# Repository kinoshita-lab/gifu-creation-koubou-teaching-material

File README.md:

# gifu-creation-koubou-teaching-material
こちらは、オンラインワークショップ 岐阜クリエーション工房2022 2. 自分の電子楽器をデザインしよう！
https://sites.google.com/iamas.ac.jp/gifu-creation-workshop/2022?authuser=0#h.r4l3rx4b2rmy
で配布した教材のリポジトリです。

## 教材基板ハードウェアの設計図(pdf)
- [ベースボードの回路図](https://github.com/kinoshita-lab/gifu-creation-koubou-teaching-material/blob/main/hardware/base-pcb/gifu-creation-koubou-teaching-material-schematics.pdf)
- [ベースボードの基板](https://github.com/kinoshita-lab/gifu-creation-koubou-teaching-material/blob/main/hardware/base-pcb/gifu-creation-koubou-teaching-material-pcb.pdf)

- [フィルターの回路図](https://github.com/kinoshita-lab/gifu-creation-koubou-teaching-material/blob/main/hardware/vcf-13700/vcf-13700-schematics.pdf)
- [フィルターの基板](https://github.com/kinoshita-lab/gifu-creation-koubou-teaching-material/blob/main/hardware/vcf-13700/vcf-13700-pcb.pdf)

- [ディレイの回路図](https://github.com/kinoshita-lab/gifu-creation-koubou-teaching-material/blob/main/hardware/PT2399delay/PT2399delay-schematics.pdf)
- [ディレイの基板](https://github.com/kinoshita-lab/gifu-creation-koubou-teaching-material/blob/main/hardware/PT2399delay/PT2399delay-pcb.pdf)

## マイコンのソフト
[Platform IO](https://platformio.org/) という開発環境を使っています。
- [ライブラリを含んだ全体](https://github.com/kinoshita-lab/gifu-creation-koubou-teaching-material/tree/main/software/gifu-creation-koubou-teathing-material-esp32)
- [一番重要な内容が書いてあるファイル](https://github.com/kinoshita-lab/gifu-creation-koubou-teaching-material/blob/main/software/gifu-creation-koubou-teathing-material-esp32/src/main.cpp)

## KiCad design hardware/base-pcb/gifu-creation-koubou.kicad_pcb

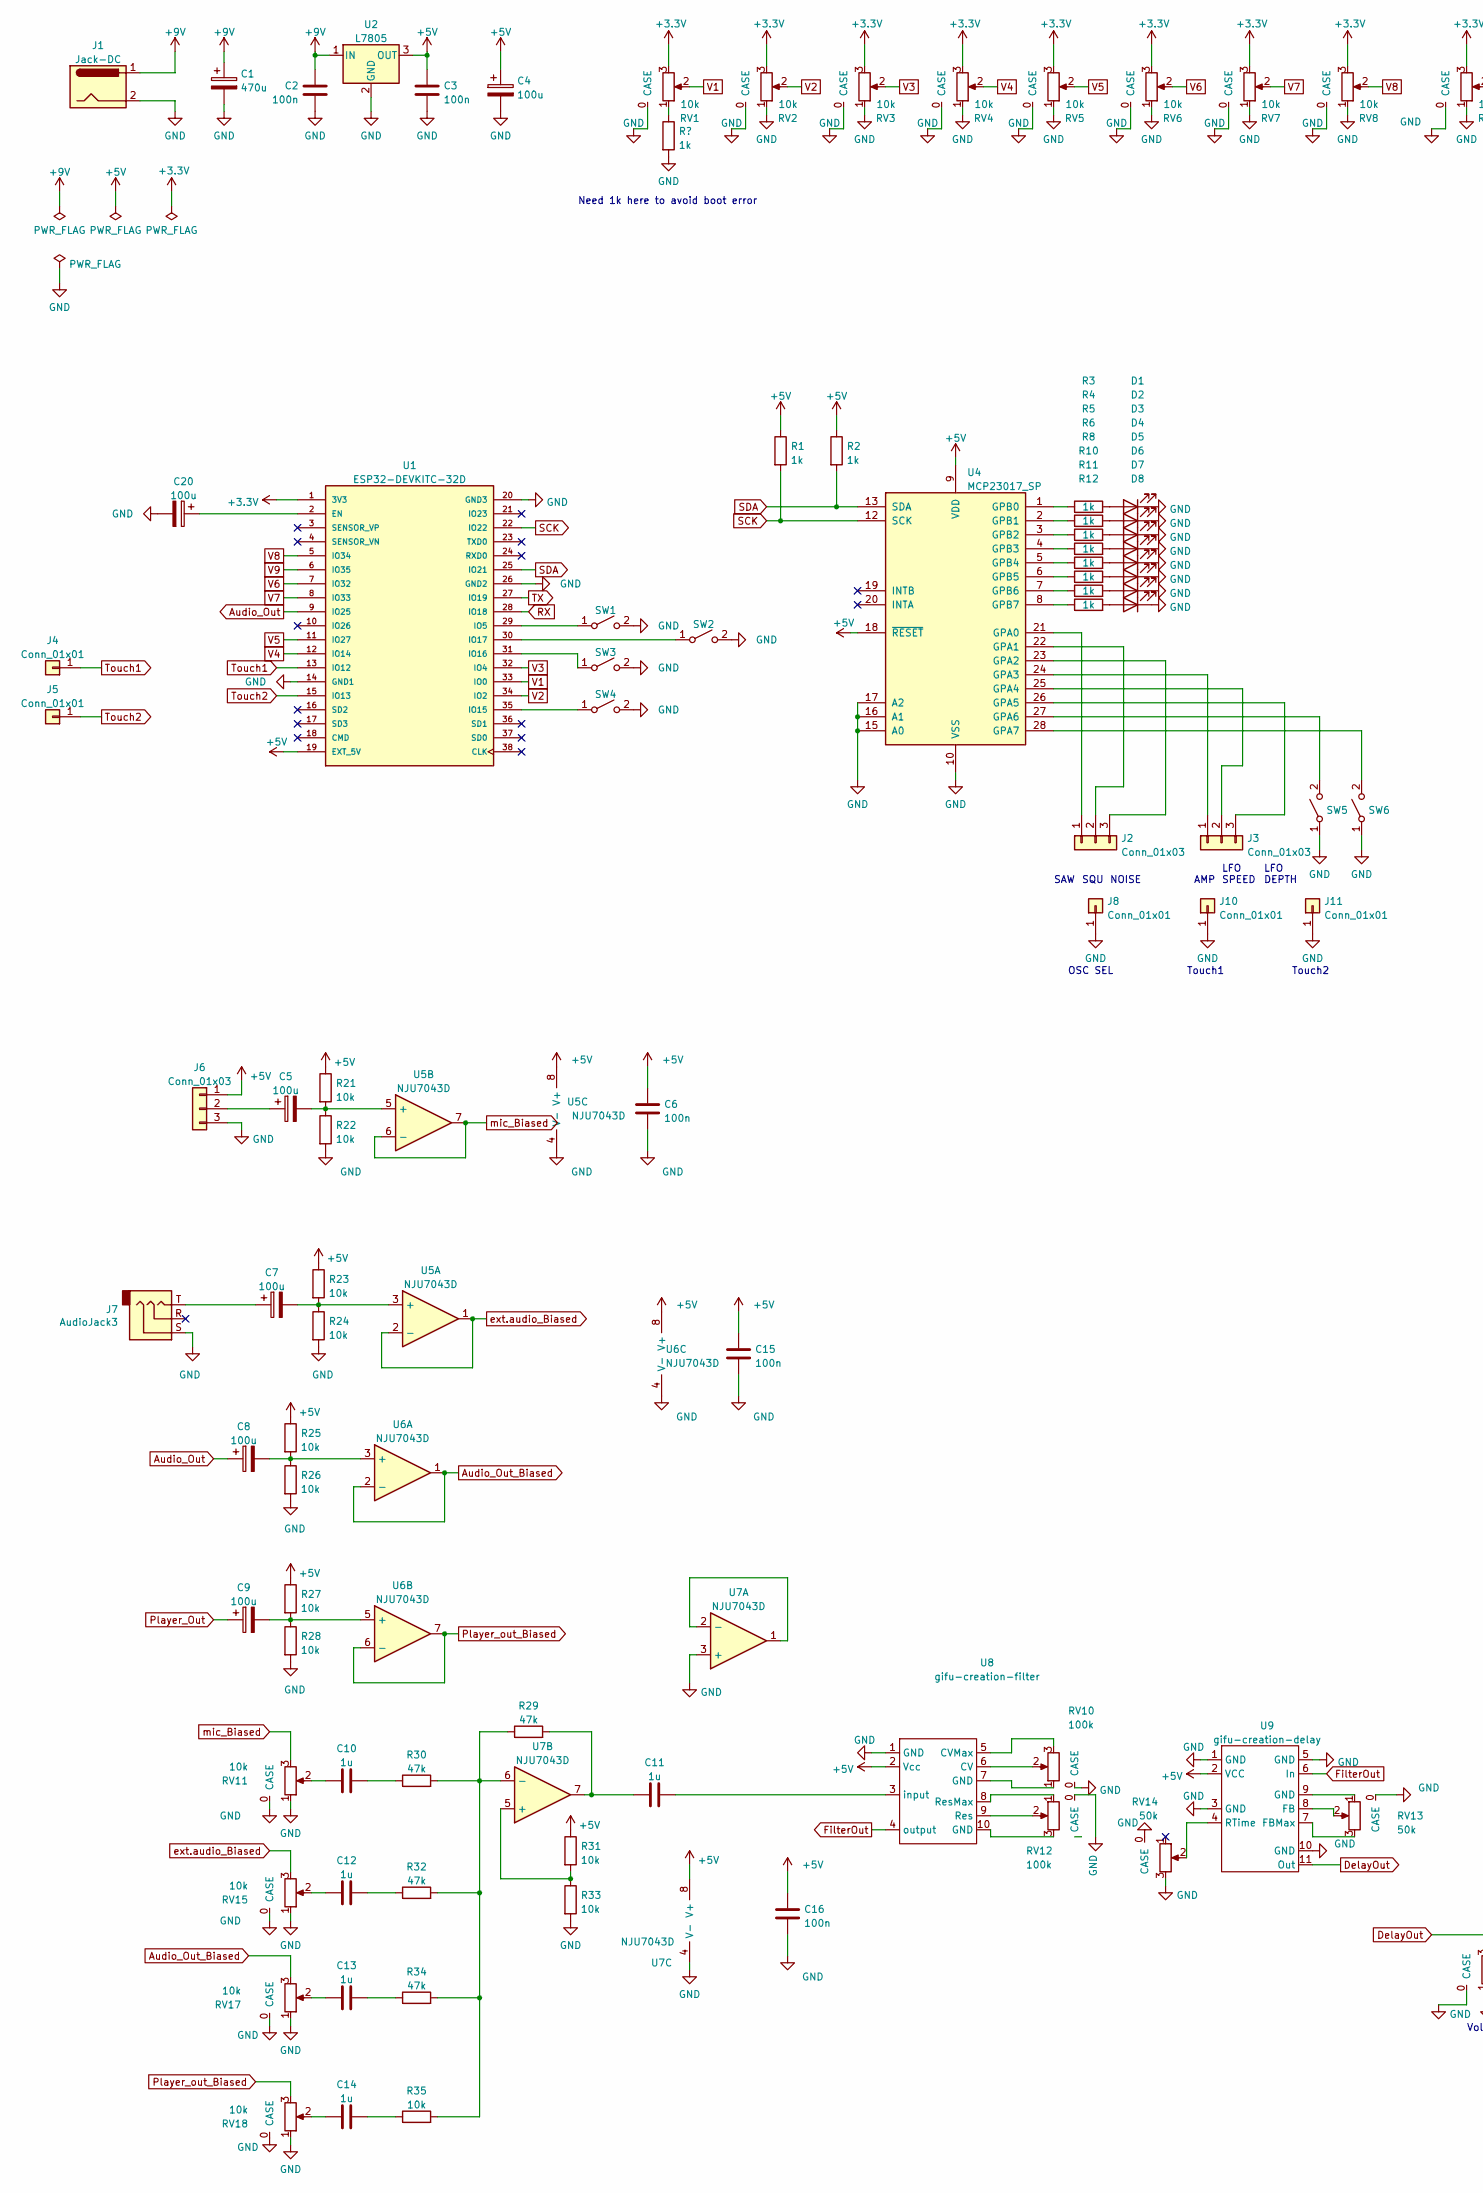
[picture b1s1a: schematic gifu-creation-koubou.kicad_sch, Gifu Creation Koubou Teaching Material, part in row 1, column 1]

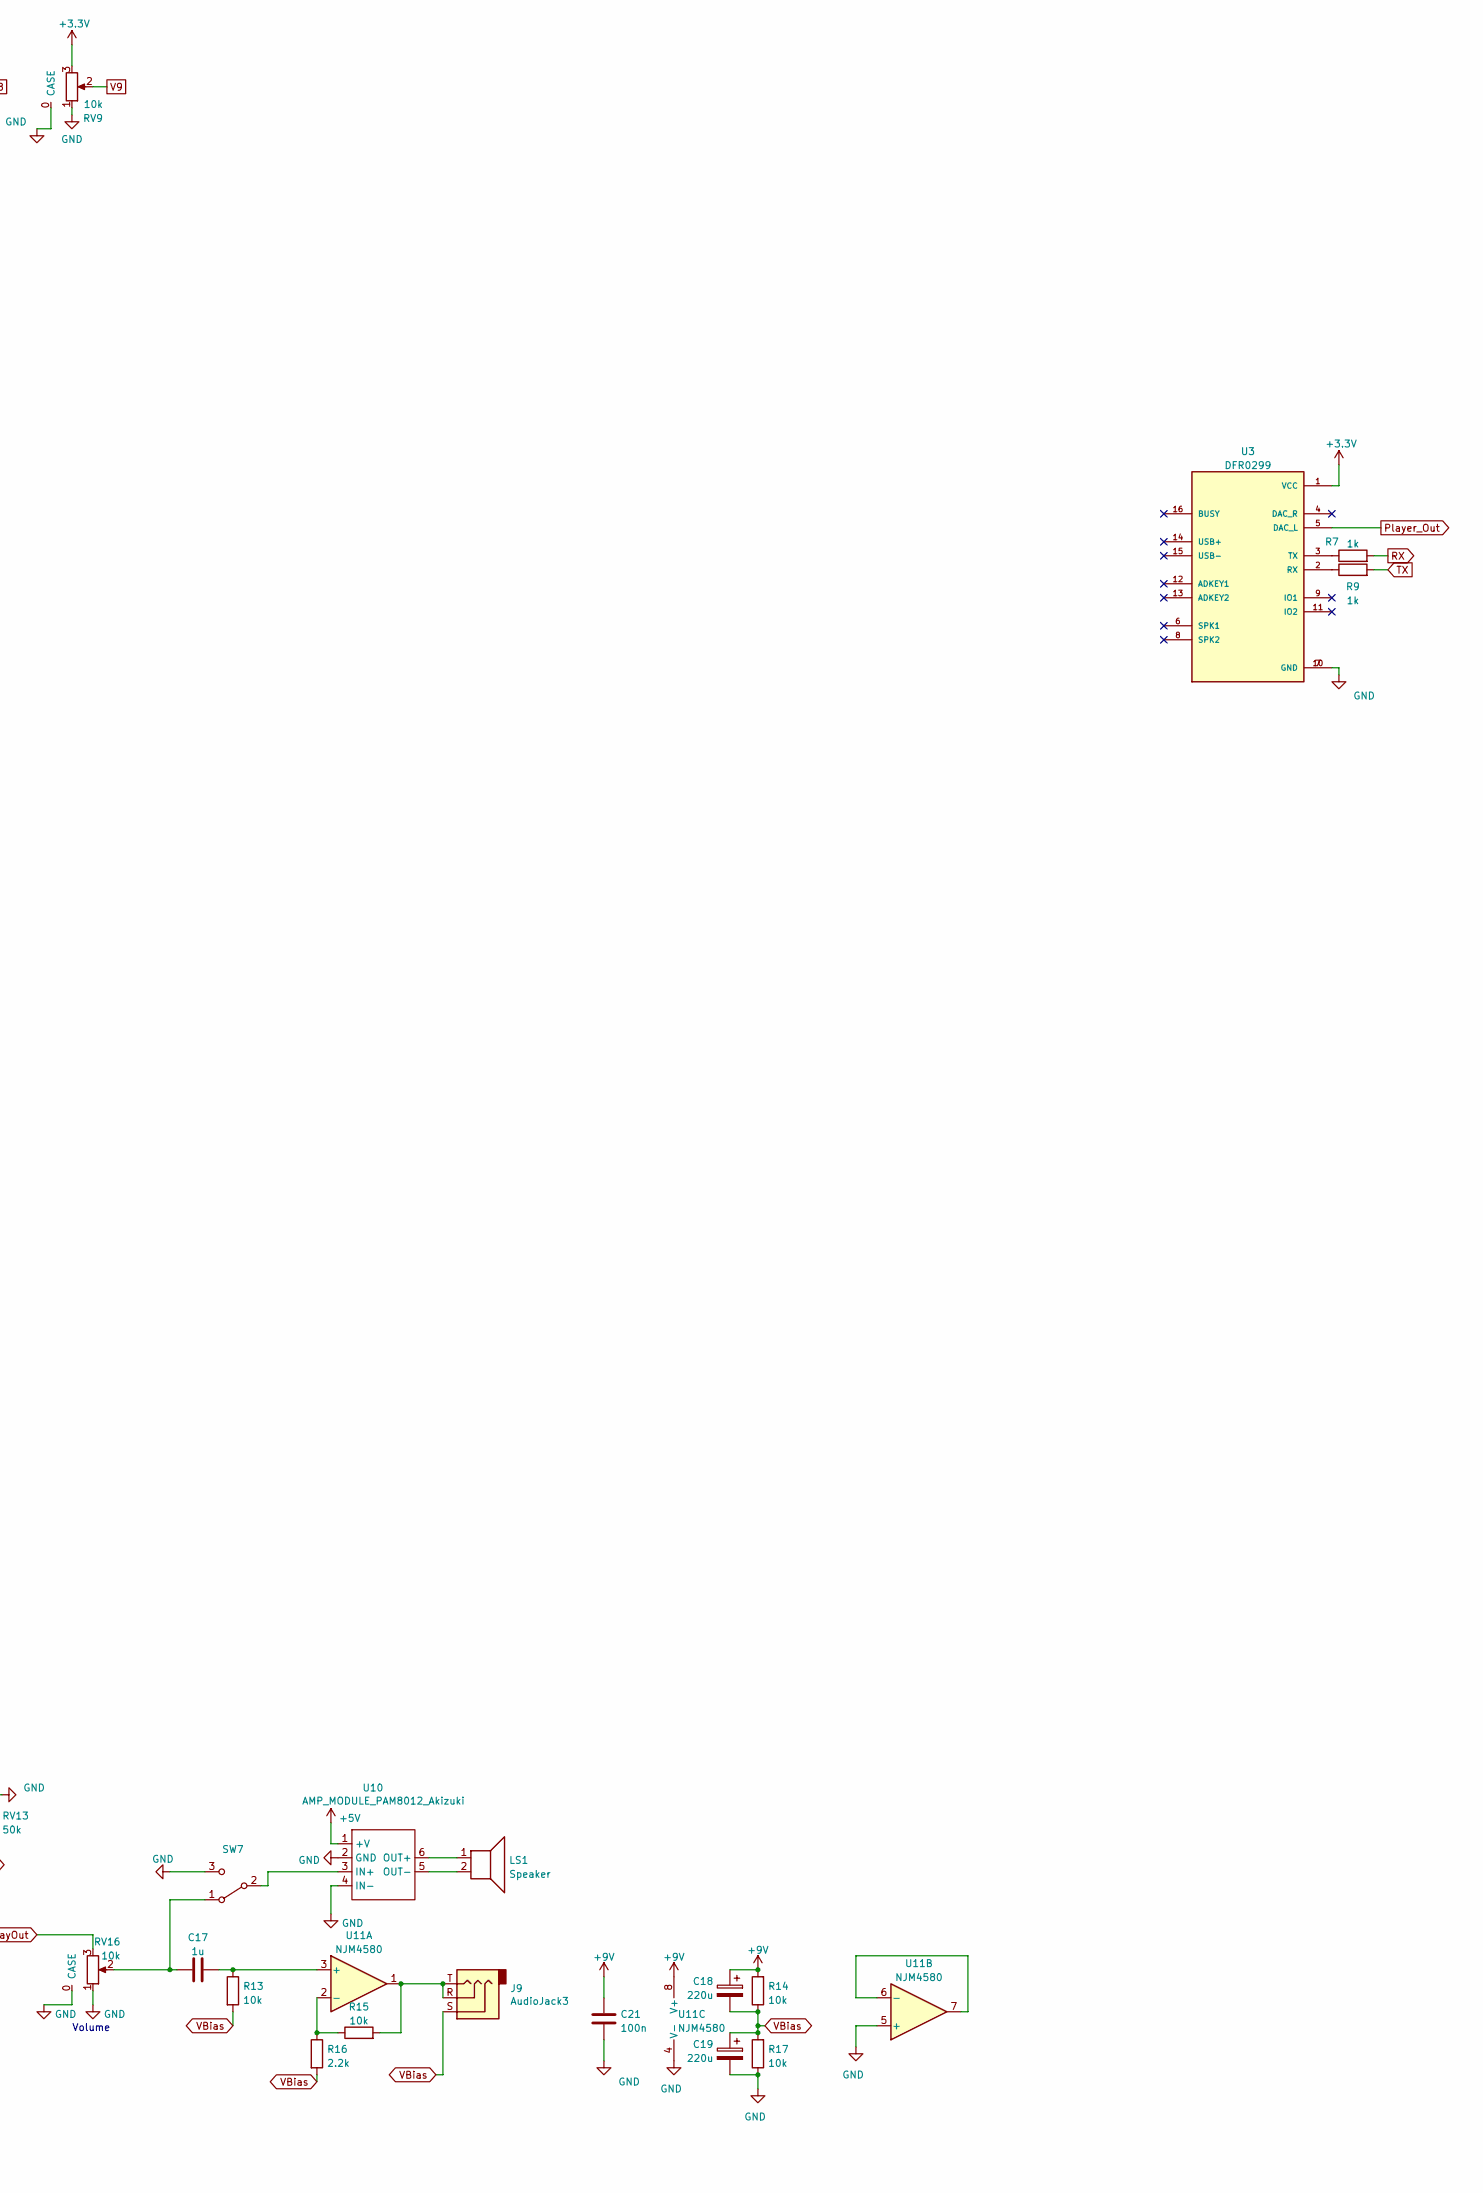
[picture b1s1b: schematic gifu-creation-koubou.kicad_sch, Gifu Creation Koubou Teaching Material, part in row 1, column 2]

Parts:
C1: 470u; CP_Radial_D8.0mm_P3.50mm
C2, C3, C6, C15, C16, C21: 100n; C_Disc_D5.0mm_W2.5mm_P5.00mm
C4, C5, C7, C8, C9, C20: 100u; CP_Radial_D5.0mm_P2.00mm
C10, C11, C12, C13, C14, C17: 1u; C_Disc_D5.0mm_W2.5mm_P5.00mm
C18, C19: 220u; CP_Radial_D5.0mm_P2.00mm
D1, D2, D3, D4, D5, D6, D7, D8: LED; LED_D3.0mm
J1: Jack-DC; DCJ3P-14.2X11.0X9.0MM
J2, J3, J6: Conn_01x03; PinHeader_1x03_P2.54mm_Vertical
J4, J5: Conn_01x01; touch_electrode
J7, J9: AudioJack3; 3.5mm_Stereo_TRS_PJ-3210-4A_and_ST-005-G; LCSC C136686
J8, J10, J11: Conn_01x01; PinSocket_1x01_P2.54mm_Vertical
LS1: Speaker; Speaker_UGSM30B-8-01
R1, R2, R3, R4, R5, R6, R7, R8, R9, R10, R11, R12: 1k; R_Axial_DIN0207_L6.3mm_D2.5mm_P2.54mm_Vertical
R13, R14, R15, R17, R21, R22, R23, R24, R25, R26, R27, R28, R31, R33, R35: 10k; R_Axial_DIN0207_L6.3mm_D2.5mm_P2.54mm_Vertical
R16: 2.2k; R_Axial_DIN0207_L6.3mm_D2.5mm_P2.54mm_Vertical
R29, R30, R32, R34: 47k; R_Axial_DIN0207_L6.3mm_D2.5mm_P2.54mm_Vertical
RV1, RV2, RV3, RV4, RV5, RV6, RV7, RV8, RV9, RV11, RV15, RV16, RV17, RV18: 10k; Potentiometer_Alps_RK09K_Horizontal_CORRECTED
RV10, RV12: 100k; Potentiometer_Alps_RK09K_Horizontal_CORRECTED
RV13, RV14: 50k; Potentiometer_Alps_RK09K_Horizontal_CORRECTED
SW1, SW2, SW3, SW4, SW5, SW6: SW_SPST; SW_Tactile_6mm_x_6mm_Futsuuno_Akizuki_nadoniaruyatsu
SW7: SW_SPDT; Switch_Toggle_PCB_Mount_Akizuki_2MS1-T1-B4-M2-Q-E
U1: ESP32-DEVKITC-32D; MODULE_ESP32-DEVKITC-32D; PARTREV 4
U2: L7805; TO-220F-3_Vertical
U3: DFR0299; MODULE_DFR0299
U4: MCP23017_SP; DIP-28_W7.62mm
U5, U6, U7: NJU7043D; DIP-8_W7.62mm
U8: gifu-creation-filter; filter_13700
U9: gifu-creation-delay; delay
U10: AMP_MODULE_PAM8012_Akizuki; AMP_Module_PAM8012_Akizuki
U11: NJM4580; DIP-8_W7.62mm

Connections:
+3V3: RV1.3, RV2.3, RV3.3, RV4.3, RV5.3, RV6.3, RV7.3, RV8.3, RV9.3, U1.1 (3V3), U3.1 (VCC)
+5V: C3.1, C4.1, C6.1, C15.1, C16.1, J6.1, R1.1, R2.1, R21.1, R23.1, R25.1, R27.1, R31.1, U1.19 (EXT_5V), U2.3 (OUT), U4.9 (VDD), U4.18 (~RESET), U5.8 (V+), U6.8 (V+), U7.8 (V+), U8.2 (Vcc), U9.2 (VCC), U10.1 (+V)
+9V: C1.1, C2.1, C18.1, C21.1, J1.1, R14.2, U2.1 (IN), U11.8 (V+)
Audio_Out: C8.1, U1.9 (IO25)
Audio_Out_Biased: RV17.3, U6.1, U6.2 (-)
DelayOut: RV16.3, U9.11 (Out)
FilterOut: U8.4 (output), U9.6 (In)
GND: C1.2, C2.2, C3.2, C4.2, C6.2, C15.2, C16.2, C19.2, C20.2, C21.2, D1.1 (K), D2.1 (K), D3.1 (K), D4.1 (K), D5.1 (K), D6.1 (K), D7.1 (K), D8.1 (K), J1.2, J6.3, J7.S, J8.1, J10.1, J11.1, R17.1, R22.2, R24.2, R26.2, R28.2, R33.2, RV1.0 (CASE), RV1.1, RV2.0 (CASE), RV2.1, RV3.0 (CASE), RV3.1, RV4.0 (CASE), RV4.1, RV5.0 (CASE), RV5.1, RV6.0 (CASE), RV6.1, RV7.0 (CASE), RV7.1, RV8.0 (CASE), RV8.1, RV9.0 (CASE), RV9.1, RV10.0 (CASE), RV11.0 (CASE), RV11.1, RV12.0 (CASE), RV13.0 (CASE), RV14.0 (CASE), RV14.3, RV15.0 (CASE), RV15.1, RV16.0 (CASE), RV16.1, RV17.0 (CASE), RV17.1, RV18.0 (CASE), RV18.1, SW1.2 (B), SW2.2 (B), SW3.2 (B), SW4.2 (B), SW5.1 (A), SW6.1 (A), SW7.3 (C), U1.14 (GND1), U1.20 (GND3), U1.26 (GND2), U2.2 (GND), U3.7 (GND), U3.10 (GND), U4.10 (VSS), U4.15 (A0), U4.16 (A1), U4.17 (A2), U5.4 (V-), U6.4 (V-), U7.3 (+), U7.4 (V-), U8.1 (GND), U9.1 (GND), U9.3 (GND), U9.5 (GND), U9.10 (GND), U10.2 (GND), U10.4 (IN-), U11.4 (V-), U11.5 (+)
unnamed: C5.1, J6.2
unnamed: C5.2, R21.2, R22.1, U5.5 (+)
unnamed: C7.1, J7.T
unnamed: C7.2, R23.2, R24.1, U5.3 (+)
unnamed: C8.2, R25.2, R26.1, U6.3 (+)
unnamed: C9.2, R27.2, R28.1, U6.5 (+)
unnamed: C10.1, RV11.2
unnamed: C10.2, R30.1
unnamed: C11.1, R29.2, U7.7
unnamed: C11.2, U8.3 (input)
unnamed: C12.1, RV15.2
unnamed: C12.2, R32.1
unnamed: C13.1, RV17.2
unnamed: C13.2, R34.1
unnamed: C14.1, RV18.2
unnamed: C14.2, R35.1
unnamed: C17.1, RV16.2, SW7.1 (A)
unnamed: C17.2, R13.1, U11.3 (+)
unnamed: D1.2 (A), R3.2
unnamed: D2.2 (A), R4.2
unnamed: D3.2 (A), R5.2
unnamed: D4.2 (A), R6.2
unnamed: D5.2 (A), R8.2
unnamed: D6.2 (A), R10.2
unnamed: D7.2 (A), R11.2
unnamed: D8.2 (A), R12.2
unnamed: J2.1, U4.21 (GPA0)
unnamed: J2.2, U4.22 (GPA1)
unnamed: J2.3, U4.23 (GPA2)
unnamed: J3.1, U4.24 (GPA3)
unnamed: J3.2, U4.25 (GPA4)
unnamed: J3.3, U4.26 (GPA5)
unnamed: J9.R, J9.T, R15.2, U11.1
unnamed: LS1.1, U10.6 (OUT+)
unnamed: LS1.2, U10.5 (OUT-)
unnamed: R3.1, U4.1 (GPB0)
unnamed: R4.1, U4.2 (GPB1)
unnamed: R5.1, U4.3 (GPB2)
unnamed: R6.1, U4.4 (GPB3)
unnamed: R7.1, U3.3 (TX)
unnamed: R8.1, U4.5 (GPB4)
unnamed: R9.1, U3.2 (RX)
unnamed: R10.1, U4.6 (GPB5)
unnamed: R11.1, U4.7 (GPB6)
unnamed: R12.1, U4.8 (GPB7)
unnamed: R15.1, R16.1, U11.2 (-)
unnamed: R29.1, R30.2, R32.2, R34.2, R35.2, U7.6 (-)
unnamed: R31.2, R33.1, U7.5 (+)
unnamed: RV10.1, U8.7 (GND)
unnamed: RV10.2, U8.6 (CV)
unnamed: RV10.3, U8.5 (CVMax)
unnamed: RV12.1, U8.8 (ResMax)
unnamed: RV12.2, U8.9 (Res)
unnamed: RV12.3, U8.10 (GND)
unnamed: RV13.1, U9.9 (GND)
unnamed: RV13.2, U9.8 (FB)
unnamed: RV13.3, U9.7 (FBMax)
unnamed: RV14.2, U9.4 (RTime)
unnamed: SW1.1 (A), U1.29 (IO5)
unnamed: SW2.1 (A), U1.30 (IO17)
unnamed: SW3.1 (A), U1.31 (IO16)
unnamed: SW4.1 (A), U1.35 (IO15)
unnamed: SW5.2 (B), U4.27 (GPA6)
unnamed: SW6.2 (B), U4.28 (GPA7)
unnamed: SW7.2 (B), U10.3 (IN+)
unnamed: C20.1, U1.2 (EN)
unnamed: U7.1, U7.2 (-)
unnamed: U11.6 (-), U11.7
Player_Out: C9.1, U3.5 (DAC_L)
Player_out_Biased: RV18.3, U6.6 (-), U6.7
RX: R7.2, U1.28 (IO18)
SCK: R1.2, U1.22 (IO22), U4.12 (SCK)
SDA: R2.2, U1.25 (IO21), U4.13 (SDA)
TX: R9.2, U1.27 (IO19)
Touch1: J4.1, U1.13 (IO12)
Touch2: J5.1, U1.15 (IO13)
V1: RV1.2, U1.33 (IO0)
V2: RV2.2, U1.34 (IO2)
V3: RV3.2, U1.32 (IO4)
V4: RV4.2, U1.12 (IO14)
V5: RV5.2, U1.11 (IO27)
V6: RV6.2, U1.7 (IO32)
V7: RV7.2, U1.8 (IO33)
V8: RV8.2, U1.5 (IO34)
V9: RV9.2, U1.6 (IO35)
VBias: C18.2, C19.1, J9.S, R13.2, R14.1, R16.2, R17.2
ext.audio_Biased: RV15.3, U5.1, U5.2 (-)
mic_Biased: RV11.3, U5.6 (-), U5.7

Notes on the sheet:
AMP
LFO DEPTH
SQU
OSC SEL
Volume
Touch1
Touch2
Need 1k here to avoid boot error
SAW
NOISE
LFO SPEED

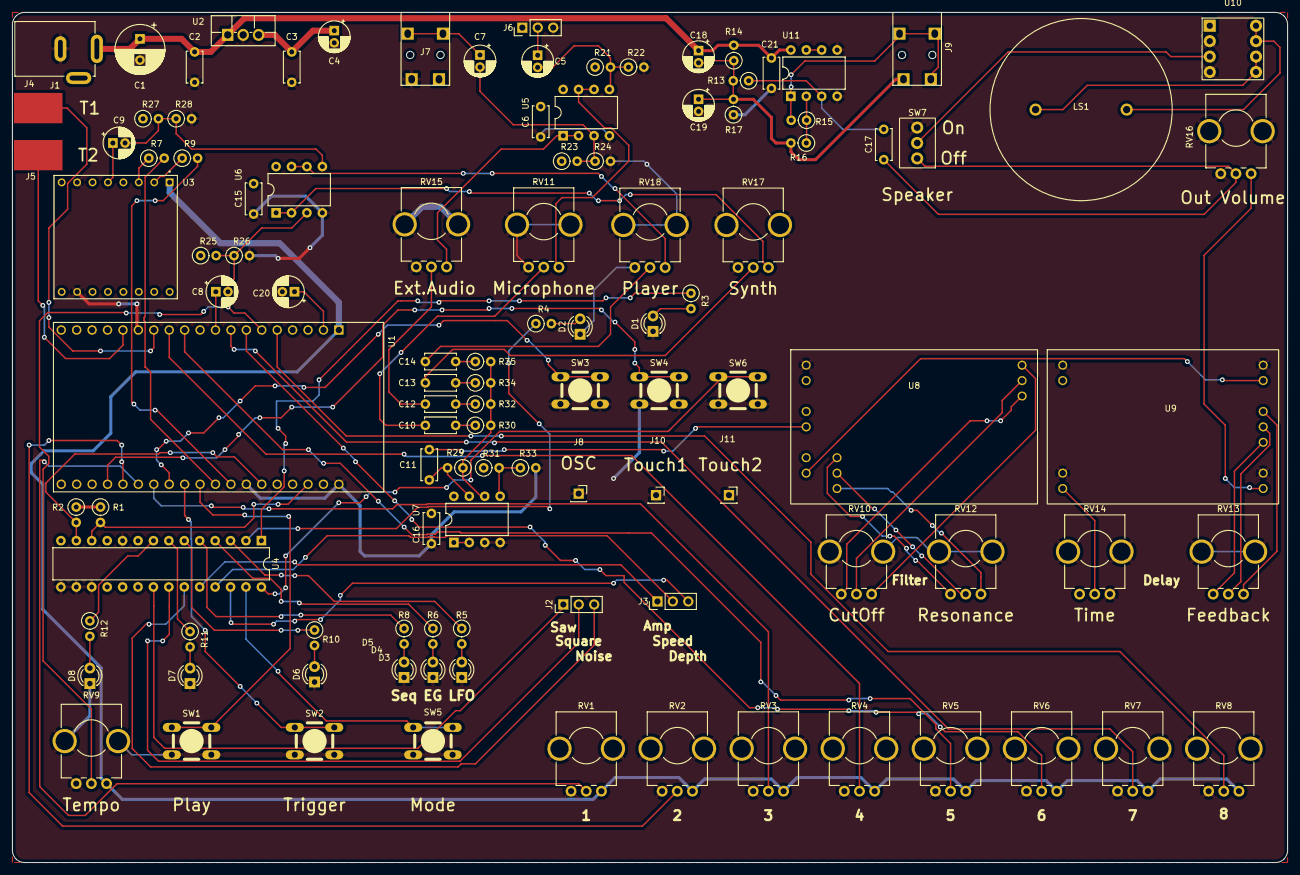
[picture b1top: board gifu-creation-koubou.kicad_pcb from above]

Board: 2 copper layers, 210.0 x 140.0 mm, 109 parts (0 on the bottom side), 96 nets.

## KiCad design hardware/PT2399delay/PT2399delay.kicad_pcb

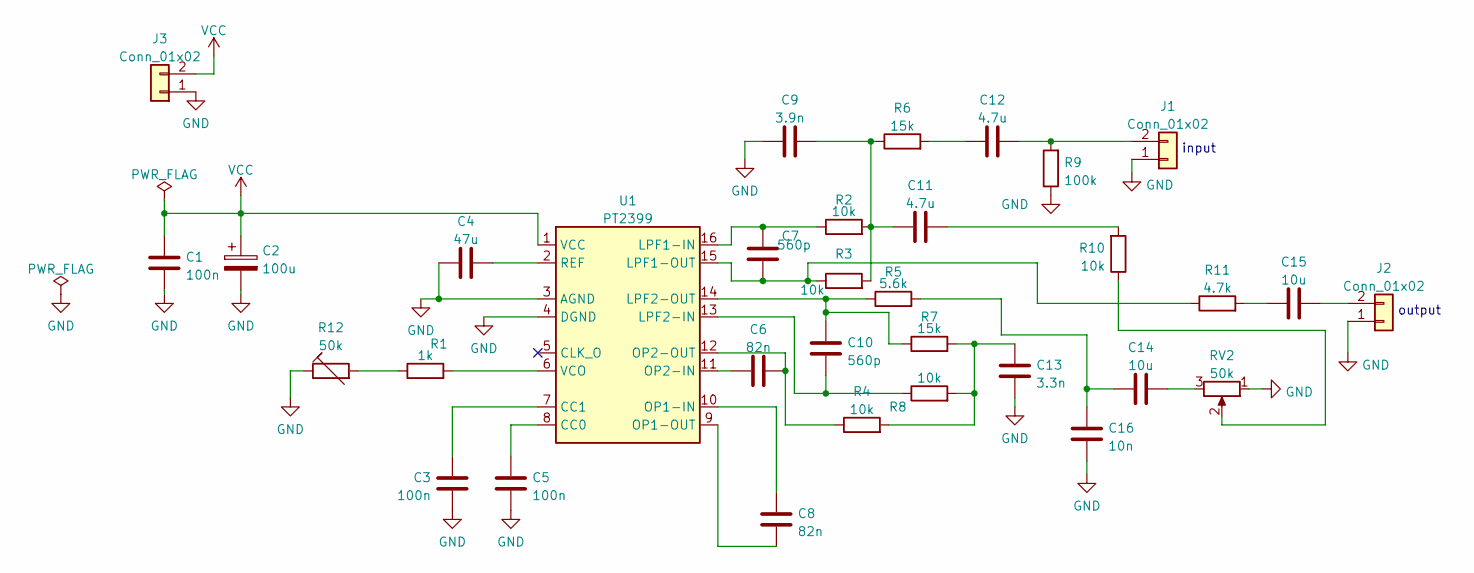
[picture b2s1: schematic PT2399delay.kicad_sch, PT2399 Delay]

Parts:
C1, C3, C5: 100n; C_0402_1005Metric_Pad0.74x0.62mm_HandSolder; LCSC C1525
C2: 100u; C_1206_3216Metric_Pad1.33x1.80mm_HandSolder; LCSC C312983
C4: 47u; C_1206_3216Metric_Pad1.33x1.80mm_HandSolder; LCSC C403725
C6, C8: 82n; C_0603_1608Metric_Pad1.08x0.95mm_HandSolder; LCSC C1951
C7, C10: 560p; C_0402_1005Metric_Pad0.74x0.62mm_HandSolder; LCSC C1539
C9: 3.9n; C_0402_1005Metric_Pad0.74x0.62mm_HandSolder; LCSC C45188
C11, C12: 4.7u; C_1206_3216Metric_Pad1.33x1.80mm_HandSolder; LCSC C29823
C13: 3.3n; C_0402_1005Metric_Pad0.74x0.62mm_HandSolder; LCSC C26404
C14: 10u; C_1206_3216Metric_Pad1.33x1.80mm_HandSolder; LCSC C13585
C15: 10u; C_1206_3216Metric_Pad1.33x1.80mm_HandSolder; LCSC C13585Copy
C16: 10n; C_0402_1005Metric_Pad0.74x0.62mm_HandSolder; LCSC C15195
J1, J2, J3: Conn_01x02; PinHeader_1x02_P2.54mm_Vertical
R1: 1k; R_0402_1005Metric_Pad0.72x0.64mm_HandSolder; LCSC C144789
R2, R3, R4, R8, R10: 10k; R_0402_1005Metric_Pad0.72x0.64mm_HandSolder; LCSC C25744
R5: 5.6k; R_0402_1005Metric_Pad0.72x0.64mm_HandSolder; LCSC C25908
R6, R7: 15k; R_0402_1005Metric_Pad0.72x0.64mm_HandSolder; LCSC C25756
R9: 100k; R_0402_1005Metric_Pad0.72x0.64mm_HandSolder; LCSC C25741
R11: 4.7k; R_0402_1005Metric_Pad0.72x0.64mm_HandSolder; LCSC C25900
R12: 50k; PinHeader_1x02_P2.54mm_Vertical
RV2: 50k; PinHeader_1x03_P2.54mm_Vertical
U1: PT2399; DIP-16_W7.62mm; LCSC C84963

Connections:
GND: C1.1, C2.2, C3.1, C4.1, C5.1, C9.2, C13.1, C16.2, J1.1, J2.1, J3.1, R9.1, R12.1, RV2.1, U1.3 (AGND), U1.4 (DGND)
unnamed: C3.2, U1.7 (CC1)
unnamed: C4.2, U1.2 (REF)
unnamed: C5.2, U1.8 (CC0)
unnamed: C6.1, U1.11 (OP2-IN)
unnamed: C6.2, R4.1, U1.12 (OP2-OUT)
unnamed: C7.1, R3.1, R11.1, U1.15 (LPF1-OUT)
unnamed: C7.2, R2.1, U1.16 (LPF1-IN)
unnamed: C8.1, U1.9 (OP1-OUT)
unnamed: C8.2, U1.10 (OP1-IN)
unnamed: C10.1, R8.1, U1.13 (LPF2-IN)
unnamed: C10.2, R5.1, R7.1, U1.14 (LPF2-OUT)
unnamed: C11.1, R10.2
unnamed: C9.1, C11.2, R2.2, R3.2, R6.1
unnamed: C12.1, J1.2, R9.2
unnamed: C12.2, R6.2
unnamed: C13.2, R4.2, R7.2, R8.2
unnamed: C14.1, RV2.3
unnamed: C14.2, C16.1, R5.2
unnamed: C15.1, J2.2
unnamed: C15.2, R11.2
unnamed: R1.1, R12.2
unnamed: R1.2, U1.6 (VCO)
unnamed: R10.1, RV2.2
VCC: C1.2, C2.1, J3.2, U1.1 (VCC)

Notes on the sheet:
input
output

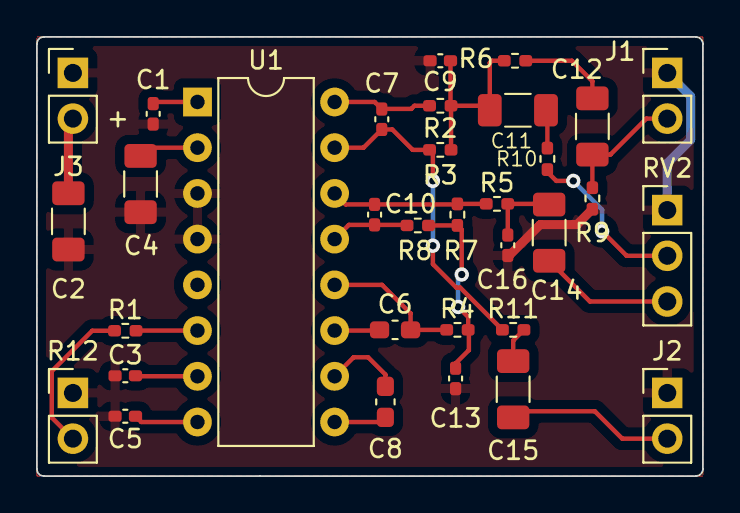
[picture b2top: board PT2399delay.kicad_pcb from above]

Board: 2 copper layers, 37.0 x 24.4 mm, 33 parts (0 on the bottom side), 25 nets.

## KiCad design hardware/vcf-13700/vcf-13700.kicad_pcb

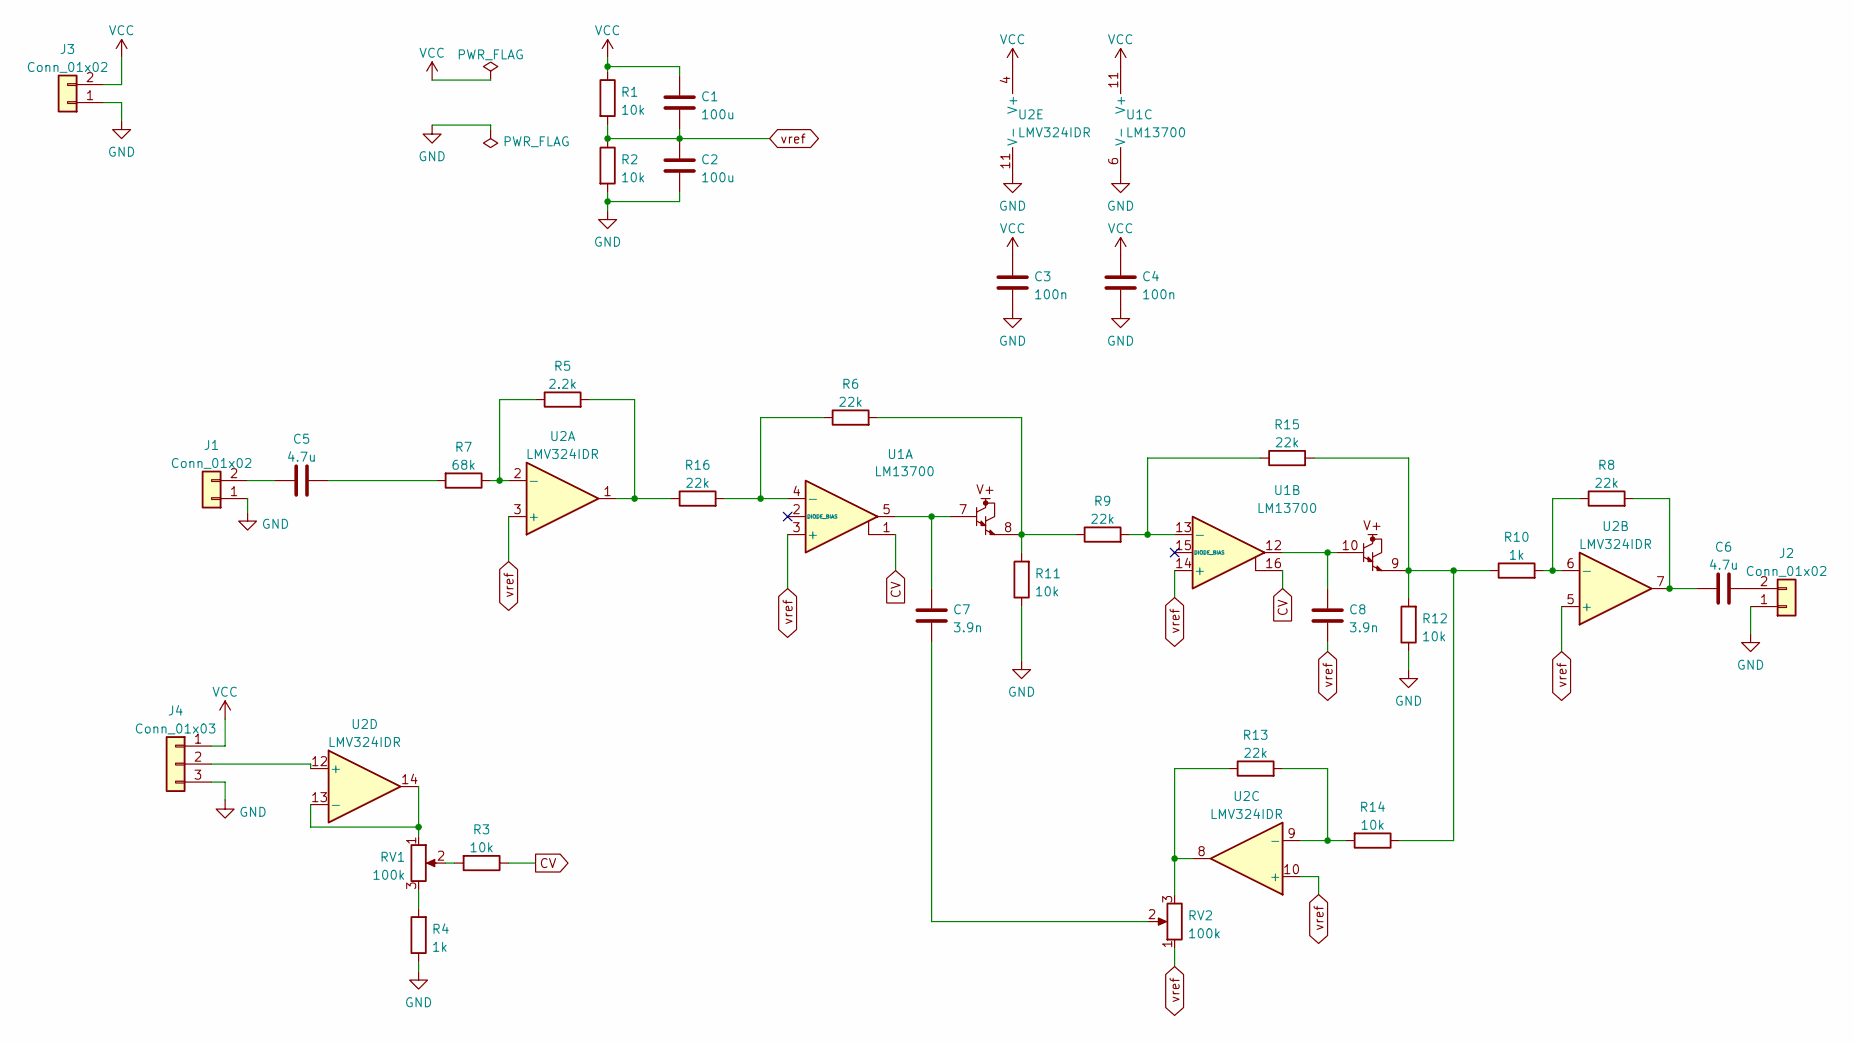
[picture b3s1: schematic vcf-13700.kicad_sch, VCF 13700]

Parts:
C1, C2: 100u; C_1206_3216Metric_Pad1.33x1.80mm_HandSolder; LCSC C15008
C3, C4: 100n; C_0402_1005Metric_Pad0.74x0.62mm_HandSolder; LCSC C1525
C5, C6: 4.7u; C_1206_3216Metric_Pad1.33x1.80mm_HandSolder; LCSC C29823
C7, C8: 3.9n; C_0402_1005Metric_Pad0.74x0.62mm_HandSolder; LCSC C45188
J1, J2, J3: Conn_01x02; PinHeader_1x02_P2.54mm_Vertical
J4: Conn_01x03; PinHeader_1x03_P2.54mm_Vertical
R1, R2, R3, R11, R12, R14: 10k; R_0402_1005Metric_Pad0.72x0.64mm_HandSolder; LCSC C25744
R4, R10: 1k; R_0402_1005Metric_Pad0.72x0.64mm_HandSolder; LCSC C144789
R5: 2.2k; R_0402_1005Metric_Pad0.72x0.64mm_HandSolder; LCSC C25879
R6, R8, R9, R13, R15, R16: 22k; R_0402_1005Metric_Pad0.72x0.64mm_HandSolder; LCSC C25768
R7: 68k; R_0402_1005Metric_Pad0.72x0.64mm_HandSolder; LCSC C36871
RV1, RV2: 100k; PinHeader_1x03_P2.54mm_Vertical
U1: LM13700; SOP-16_3.9x9.9mm_P1.27mm; LCSC C174050
U2: LMV324IDR; SO-14_3.9x8.65mm_P1.27mm; LCSC C7974

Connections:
CV: R3.1, U1.1, U1.16
GND: C2.2, C3.1, C4.1, J3.1, J4.3, R2.2, R4.1, R11.1, R12.1, U1.6 (V-), U2.11 (V-)
unnamed: C5.1, R7.2
unnamed: C5.2, J1.2
unnamed: C6.1, J2.2
unnamed: C6.2, R8.2, U2.7
unnamed: C7.1, U1.5, U1.7
unnamed: C7.2, RV2.2
unnamed: C8.1, U1.10, U1.12
unnamed: R3.2, RV1.2
unnamed: R4.2, RV1.3
unnamed: R5.1, R7.1, U2.2 (-)
unnamed: R5.2, R16.1, U2.1
unnamed: R6.1, R16.2, U1.4 (-)
unnamed: R9.2, R15.1, U1.13 (-)
unnamed: R10.1, R12.2, R14.1, R15.2, U1.9
unnamed: R8.1, R10.2, U2.6 (-)
unnamed: R6.2, R9.1, R11.2, U1.8
unnamed: R13.1, RV2.3, U2.8
unnamed: R13.2, R14.2, U2.9 (-)
unnamed: RV1.1, U2.13 (-), U2.14
unnamed: J4.2, U2.12 (+)
VCC: C1.1, C3.2, C4.2, J3.2, J4.1, R1.1, U1.11 (V+), U2.4 (V+)
vref: C1.2, C2.1, C8.2, J1.1, J2.1, R1.2, R2.1, RV2.1, U1.3 (+), U1.14 (+), U2.3 (+), U2.5 (+), U2.10 (+)

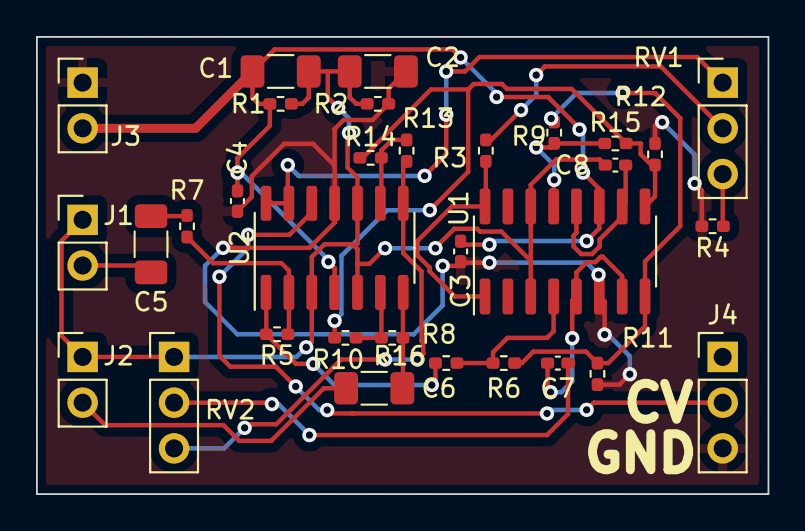
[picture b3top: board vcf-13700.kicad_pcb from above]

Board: 2 copper layers, 40.6 x 25.4 mm, 32 parts (0 on the bottom side), 24 nets.

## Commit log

2022-08-12 add hardware design file
2022-08-12 add software material as-is
2022-08-22 reorganize folder structure, add module circuits
